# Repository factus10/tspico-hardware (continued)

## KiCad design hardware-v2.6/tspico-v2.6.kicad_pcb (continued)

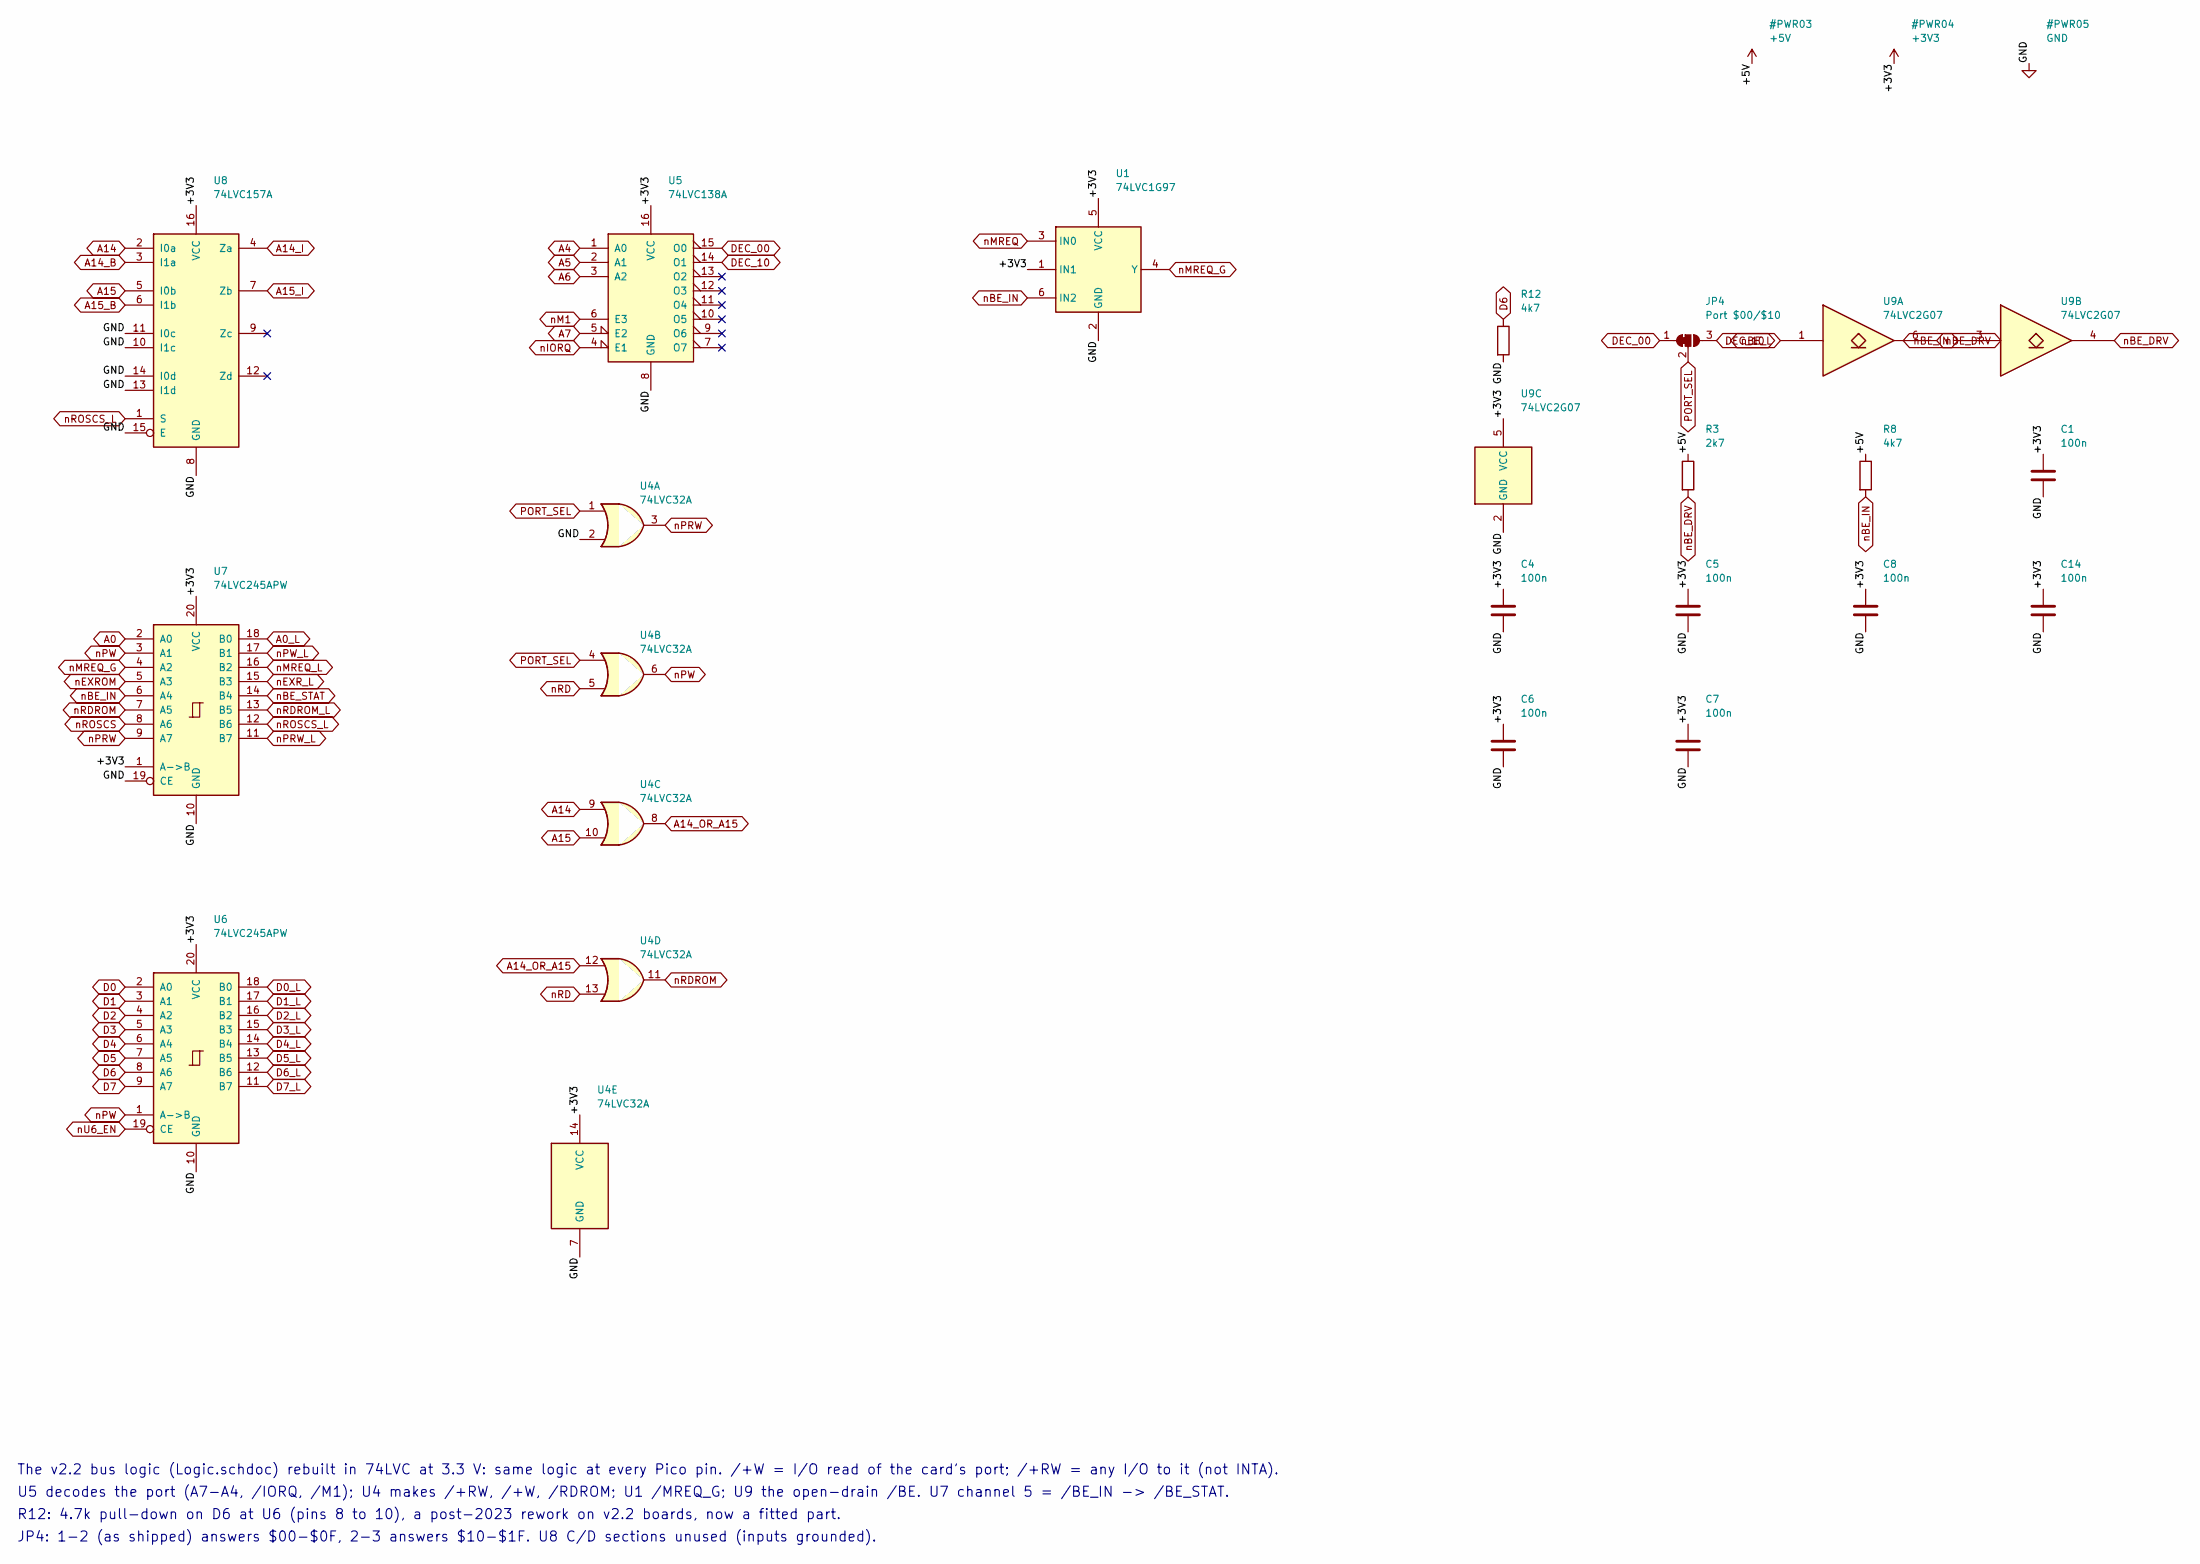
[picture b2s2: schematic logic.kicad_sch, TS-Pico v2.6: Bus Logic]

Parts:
C1, C4, C5, C6, C7, C8, C14: 100n; C_0603_1608Metric; MPN CC0603KRX7R9BB104; LCSC C14663
JP4: Port $00/$10; SolderJumper-3_P1.3mm_Bridged12_RoundedPad1.0x1.5mm_NumberL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
R3: 2k7; R_0603_1608Metric; MPN 0603WAF2701T5E; LCSC C13167
R8, R12: 4k7; R_0603_1608Metric; MPN 0603WAF4701T5E; LCSC C23162
U1: 74LVC1G97; SOT-23-6; MPN SN74LVC1G97DBVR; LCSC C128411
U4: 74LVC32A; TSSOP-14_4.4x5mm_P0.65mm; MPN 74LVC32APW,118; LCSC C6087
U5: 74LVC138A; TSSOP-16_4.4x5mm_P0.65mm; MPN SN74LVC138APWR; LCSC C485077
U6, U7: 74LVC245APW; TSSOP-20_4.4x6.5mm_P0.65mm; MPN 74LVC245APW,118; LCSC C6082
U8: 74LVC157A; TSSOP-16_4.4x5mm_P0.65mm; MPN SN74LVC157APWR; LCSC C406871
U9: 74LVC2G07; SOT-23-6; MPN 74LVC2G07GV; LCSC C19829597

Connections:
+3V3: C1.1, C4.1, C5.1, C6.1, C7.1, C8.1, C14.1, U1.1 (IN1), U1.5 (VCC), U4.14 (VCC), U5.16 (VCC), U6.20 (VCC), U7.1 (A->B), U7.20 (VCC), U8.16 (VCC), U9.5 (VCC); also elsewhere on the board
+5V: R3.1, R8.1; also elsewhere on the board
A0: U7.2 (A0); also elsewhere on the board
A0_L: U7.18 (B0); also elsewhere on the board
A4: U5.1 (A0); also elsewhere on the board
A5: U5.2 (A1); also elsewhere on the board
A6: U5.3 (A2); also elsewhere on the board
A7: U5.5 (E2); also elsewhere on the board
A14: U4.9, U8.2 (I0a); also elsewhere on the board
A14_B: U8.3 (I1a); also elsewhere on the board
A14_I: U8.4 (Za); also elsewhere on the board
A14_OR_A15: U4.8, U4.12
A15: U4.10, U8.5 (I0b); also elsewhere on the board
A15_B: U8.6 (I1b); also elsewhere on the board
A15_I: U8.7 (Zb); also elsewhere on the board
D0: U6.2 (A0); also elsewhere on the board
D0_L: U6.18 (B0); also elsewhere on the board
D1: U6.3 (A1); also elsewhere on the board
D1_L: U6.17 (B1); also elsewhere on the board
D2: U6.4 (A2); also elsewhere on the board
D2_L: U6.16 (B2); also elsewhere on the board
D3: U6.5 (A3); also elsewhere on the board
D3_L: U6.15 (B3); also elsewhere on the board
D4: U6.6 (A4); also elsewhere on the board
D4_L: U6.14 (B4); also elsewhere on the board
D5: U6.7 (A5); also elsewhere on the board
D5_L: U6.13 (B5); also elsewhere on the board
D6: R12.1, U6.8 (A6); also elsewhere on the board
D6_L: U6.12 (B6); also elsewhere on the board
D7: U6.9 (A7); also elsewhere on the board
D7_L: U6.11 (B7); also elsewhere on the board
DEC_00: JP4.1 (A), U5.15 (O0)
DEC_10: JP4.3 (B), U5.14 (O1)
GND: C1.2, C4.2, C5.2, C6.2, C7.2, C8.2, C14.2, R12.2, U1.2 (GND), U4.2, U4.7 (GND), U5.8 (GND), U6.10 (GND), U7.10 (GND), U7.19 (CE), U8.8 (GND), U8.10 (I1c), U8.11 (I0c), U8.13 (I1d), U8.14 (I0d), U8.15 (E), U9.2 (GND); also elsewhere on the board
PORT_SEL: JP4.2 (C), U4.1, U4.4
nBE_DRV: R3.2, U9.4, U9.6; also elsewhere on the board
nBE_IN: R8.2, U1.6 (IN2), U7.6 (A4), U9.3; also elsewhere on the board
nBE_L: U9.1; also elsewhere on the board
nBE_STAT: U7.14 (B4); also elsewhere on the board
nEXROM: U7.5 (A3); also elsewhere on the board
nEXR_L: U7.15 (B3); also elsewhere on the board
nIORQ: U5.4 (E1); also elsewhere on the board
nM1: U5.6 (E3); also elsewhere on the board
nMREQ: U1.3 (IN0); also elsewhere on the board
nMREQ_G: U1.4 (Y), U7.4 (A2)
nMREQ_L: U7.16 (B2); also elsewhere on the board
nPRW: U4.3, U7.9 (A7)
nPRW_L: U7.11 (B7); also elsewhere on the board
nPW: U4.6, U6.1 (A->B), U7.3 (A1)
nPW_L: U7.17 (B1); also elsewhere on the board
nRD: U4.5, U4.13; also elsewhere on the board
nRDROM: U4.11, U7.7 (A5)
nRDROM_L: U7.13 (B5); also elsewhere on the board
nROSCS: U7.8 (A6); also elsewhere on the board
nROSCS_L: U7.12 (B6), U8.1 (S); also elsewhere on the board
nU6_EN: U6.19 (CE); also elsewhere on the board

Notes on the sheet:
The v2.2 bus logic (Logic.schdoc) rebuilt in 74LVC at 3.3 V: same logic at every Pico pin. /+W = I/O read of the card's port; /+RW = any I/O to it (not INTA).
U5 decodes the port (A7-A4, /IORQ, /M1); U4 makes /+RW, /+W, /RDROM; U1 /MREQ_G; U9 the open-drain /BE. U7 channel 5 = /BE_IN -> /BE_STAT.
R12: 4.7k pull-down on D6 at U6 (pins 8 to 10), a post-2023 rework on v2.2 boards, now a fitted part.
JP4: 1-2 (as shipped) answers $00-$0F, 2-3 answers $10-$1F. U8 C/D sections unused (inputs grounded).

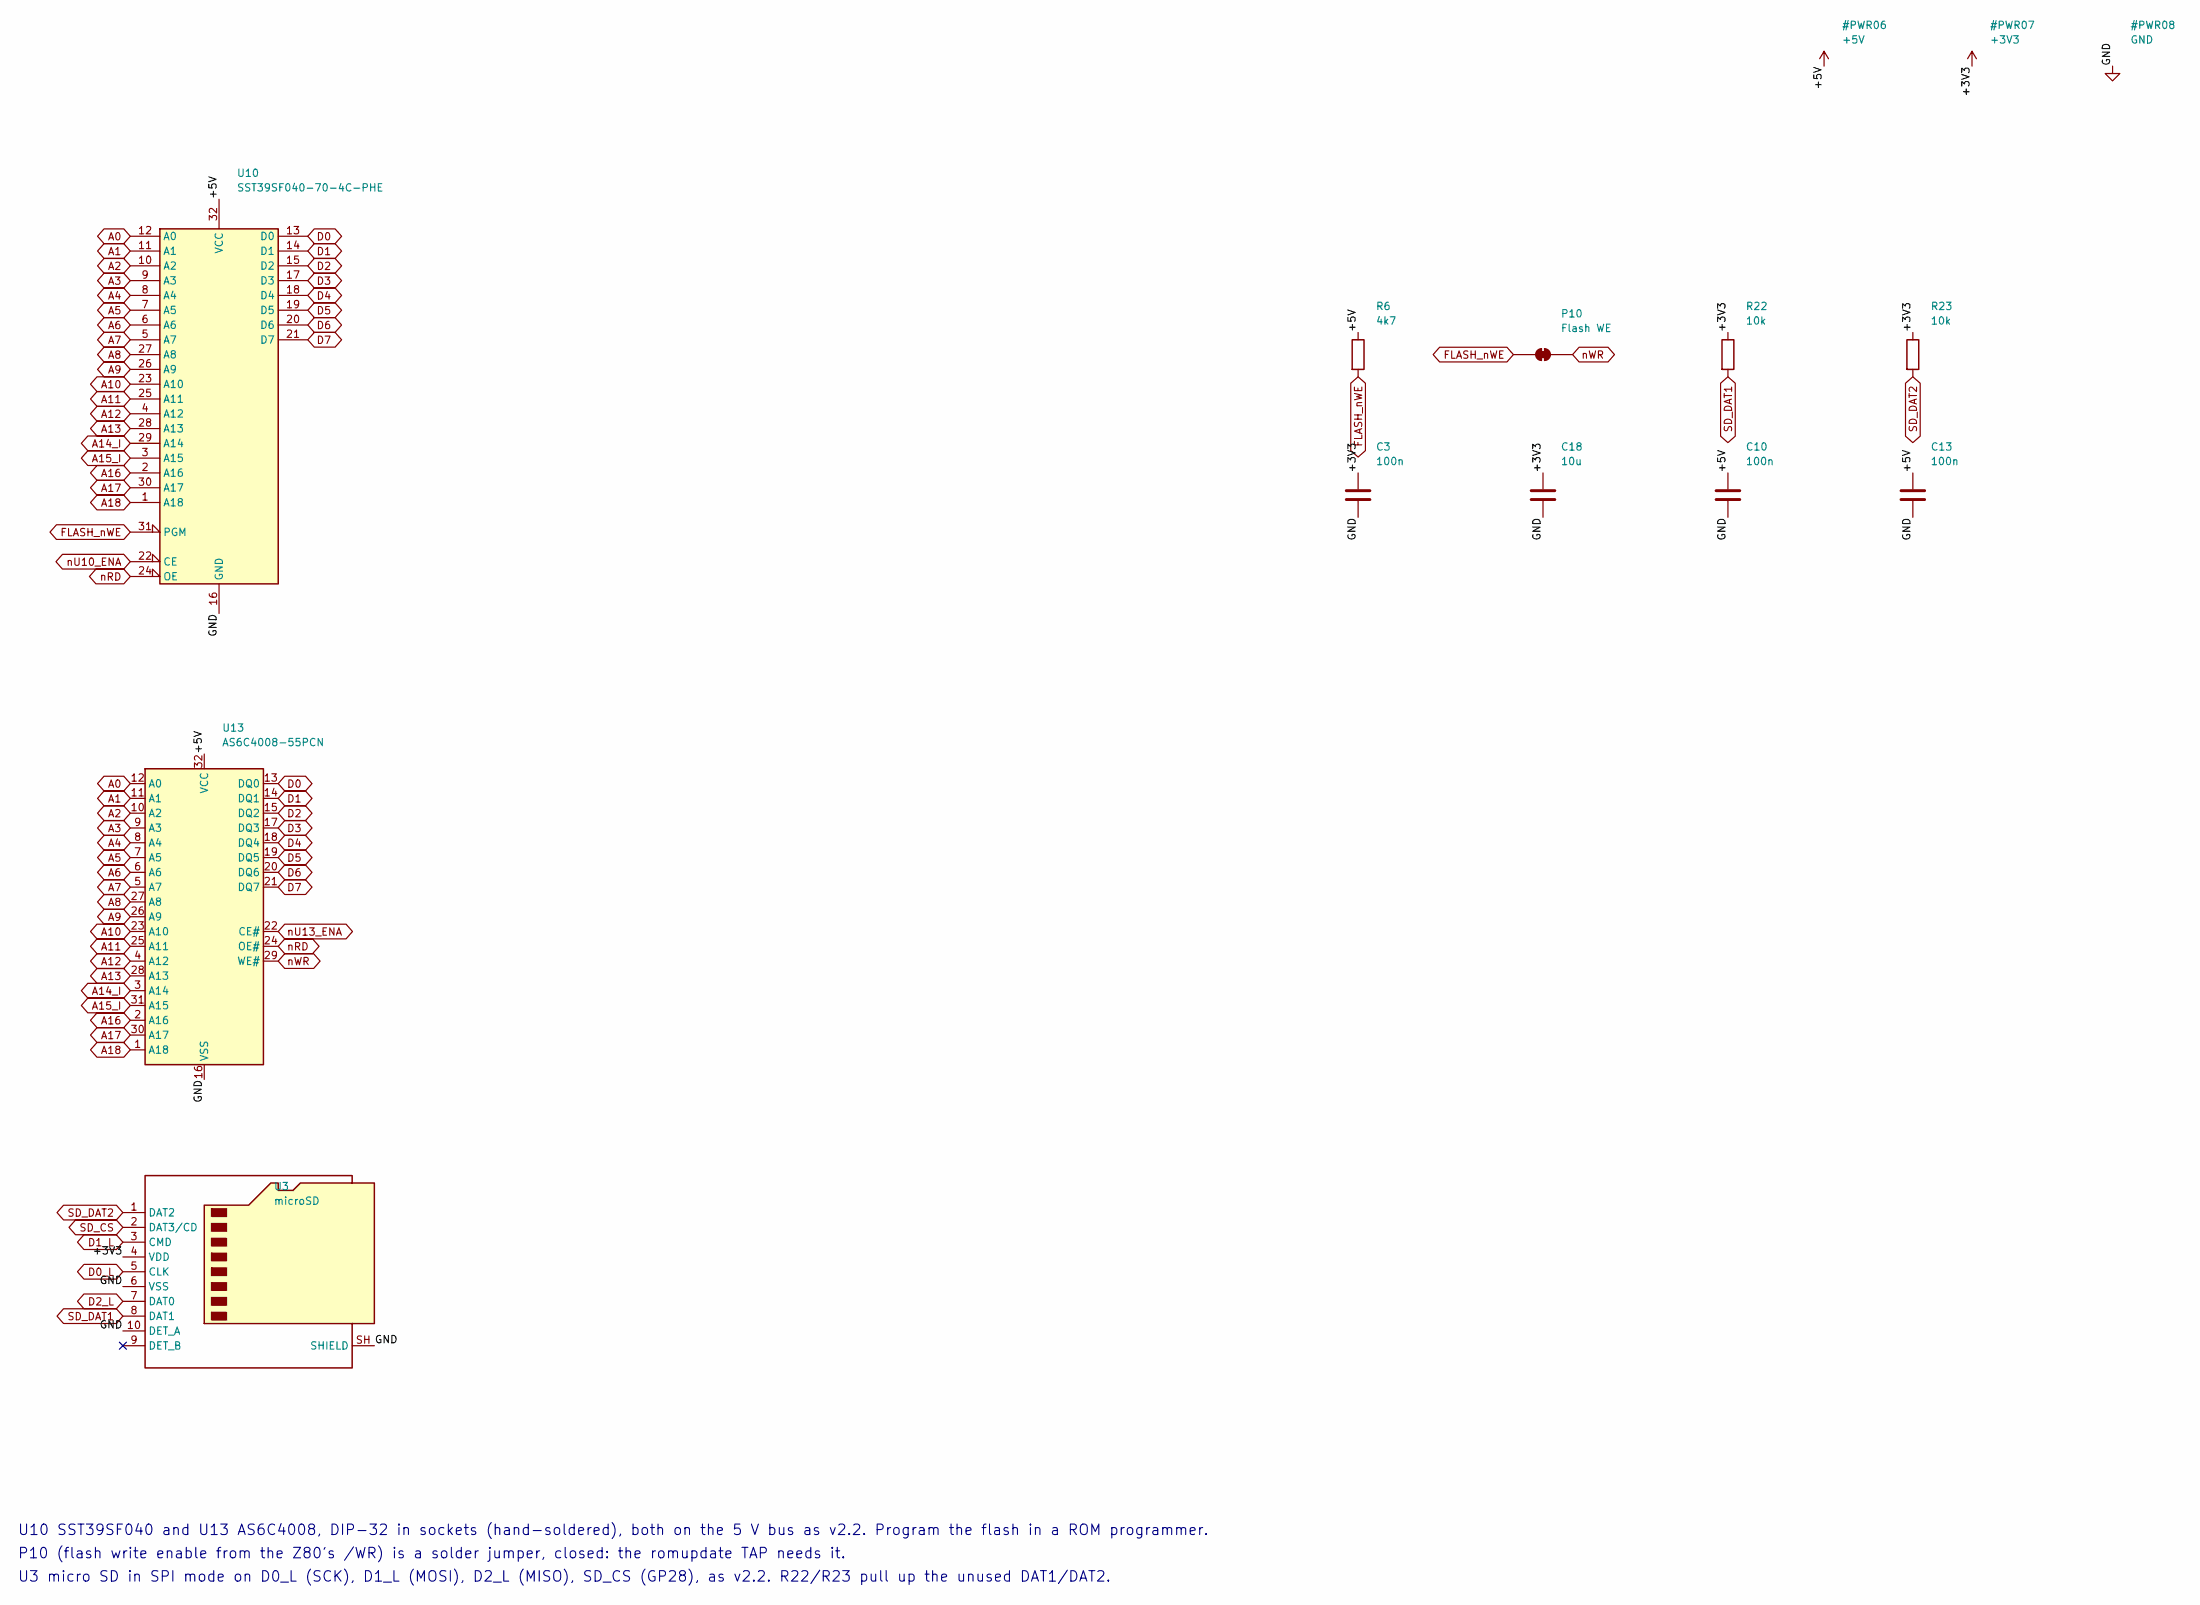
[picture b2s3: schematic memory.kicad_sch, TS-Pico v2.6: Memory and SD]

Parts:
C3, C10, C13: 100n; C_0603_1608Metric; MPN CC0603KRX7R9BB104; LCSC C14663
C18: 10u; C_0805_2012Metric; MPN CL21A106KAYNNNE; LCSC C15850
P10: Flash WE; SolderJumper-2_P1.3mm_Bridged_RoundedPad1.0x1.5mm
R6: 4k7; R_0603_1608Metric; MPN 0603WAF4701T5E; LCSC C23162
R22, R23: 10k; R_0603_1608Metric; MPN 0603WAF1002T5E; LCSC C25804
U3: microSD; microSD_TF-01A; MPN TF-01A; LCSC C91145
U10: SST39SF040-70-4C-PHE; DIP-32_W15.24mm_Socket
U13: AS6C4008-55PCN; DIP-32_W15.24mm_Socket

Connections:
+3V3: C3.1, C18.1, R22.1, R23.1, U3.4 (VDD); also elsewhere on the board
+5V: C10.1, C13.1, R6.1, U10.32 (VCC), U13.32 (VCC); also elsewhere on the board
A0: U10.12 (A0), U13.12 (A0); also elsewhere on the board
A1: U10.11 (A1), U13.11 (A1); also elsewhere on the board
A2: U10.10 (A2), U13.10 (A2); also elsewhere on the board
A3: U10.9 (A3), U13.9 (A3); also elsewhere on the board
A4: U10.8 (A4), U13.8 (A4); also elsewhere on the board
A5: U10.7 (A5), U13.7 (A5); also elsewhere on the board
A6: U10.6 (A6), U13.6 (A6); also elsewhere on the board
A7: U10.5 (A7), U13.5 (A7); also elsewhere on the board
A8: U10.27 (A8), U13.27 (A8); also elsewhere on the board
A9: U10.26 (A9), U13.26 (A9); also elsewhere on the board
A10: U10.23 (A10), U13.23 (A10); also elsewhere on the board
A11: U10.25 (A11), U13.25 (A11); also elsewhere on the board
A12: U10.4 (A12), U13.4 (A12); also elsewhere on the board
A13: U10.28 (A13), U13.28 (A13); also elsewhere on the board
A14_I: U10.29 (A14), U13.3 (A14); also elsewhere on the board
A15_I: U10.3 (A15), U13.31 (A15); also elsewhere on the board
A16: U10.2 (A16), U13.2 (A16); also elsewhere on the board
A17: U10.30 (A17), U13.30 (A17); also elsewhere on the board
A18: U10.1 (A18), U13.1 (A18); also elsewhere on the board
D0: U10.13 (D0), U13.13 (DQ0); also elsewhere on the board
D0_L: U3.5 (CLK); also elsewhere on the board
D1: U10.14 (D1), U13.14 (DQ1); also elsewhere on the board
D1_L: U3.3 (CMD); also elsewhere on the board
D2: U10.15 (D2), U13.15 (DQ2); also elsewhere on the board
D2_L: U3.7 (DAT0); also elsewhere on the board
D3: U10.17 (D3), U13.17 (DQ3); also elsewhere on the board
D4: U10.18 (D4), U13.18 (DQ4); also elsewhere on the board
D5: U10.19 (D5), U13.19 (DQ5); also elsewhere on the board
D6: U10.20 (D6), U13.20 (DQ6); also elsewhere on the board
D7: U10.21 (D7), U13.21 (DQ7); also elsewhere on the board
FLASH_nWE: P10.1 (A), R6.2, U10.31 (PGM)
GND: C3.2, C10.2, C13.2, C18.2, U3.6 (VSS), U3.10 (DET_A), U3.SH (SHIELD), U10.16 (GND), U13.16 (VSS); also elsewhere on the board
SD_CS: U3.2 (DAT3/CD); also elsewhere on the board
SD_DAT1: R22.2, U3.8 (DAT1)
SD_DAT2: R23.2, U3.1 (DAT2)
nRD: U10.24 (OE), U13.24 (OE#); also elsewhere on the board
nU10_ENA: U10.22 (CE); also elsewhere on the board
nU13_ENA: U13.22 (CE#); also elsewhere on the board
nWR: P10.2 (B), U13.29 (WE#); also elsewhere on the board

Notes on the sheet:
U10 SST39SF040 and U13 AS6C4008, DIP-32 in sockets (hand-soldered), both on the 5 V bus as v2.2. Program the flash in a ROM programmer.
P10 (flash write enable from the Z80's /WR) is a solder jumper, closed: the romupdate TAP needs it.
U3 micro SD in SPI mode on D0_L (SCK), D1_L (MOSI), D2_L (MISO), SD_CS (GP28), as v2.2. R22/R23 pull up the unused DAT1/DAT2.

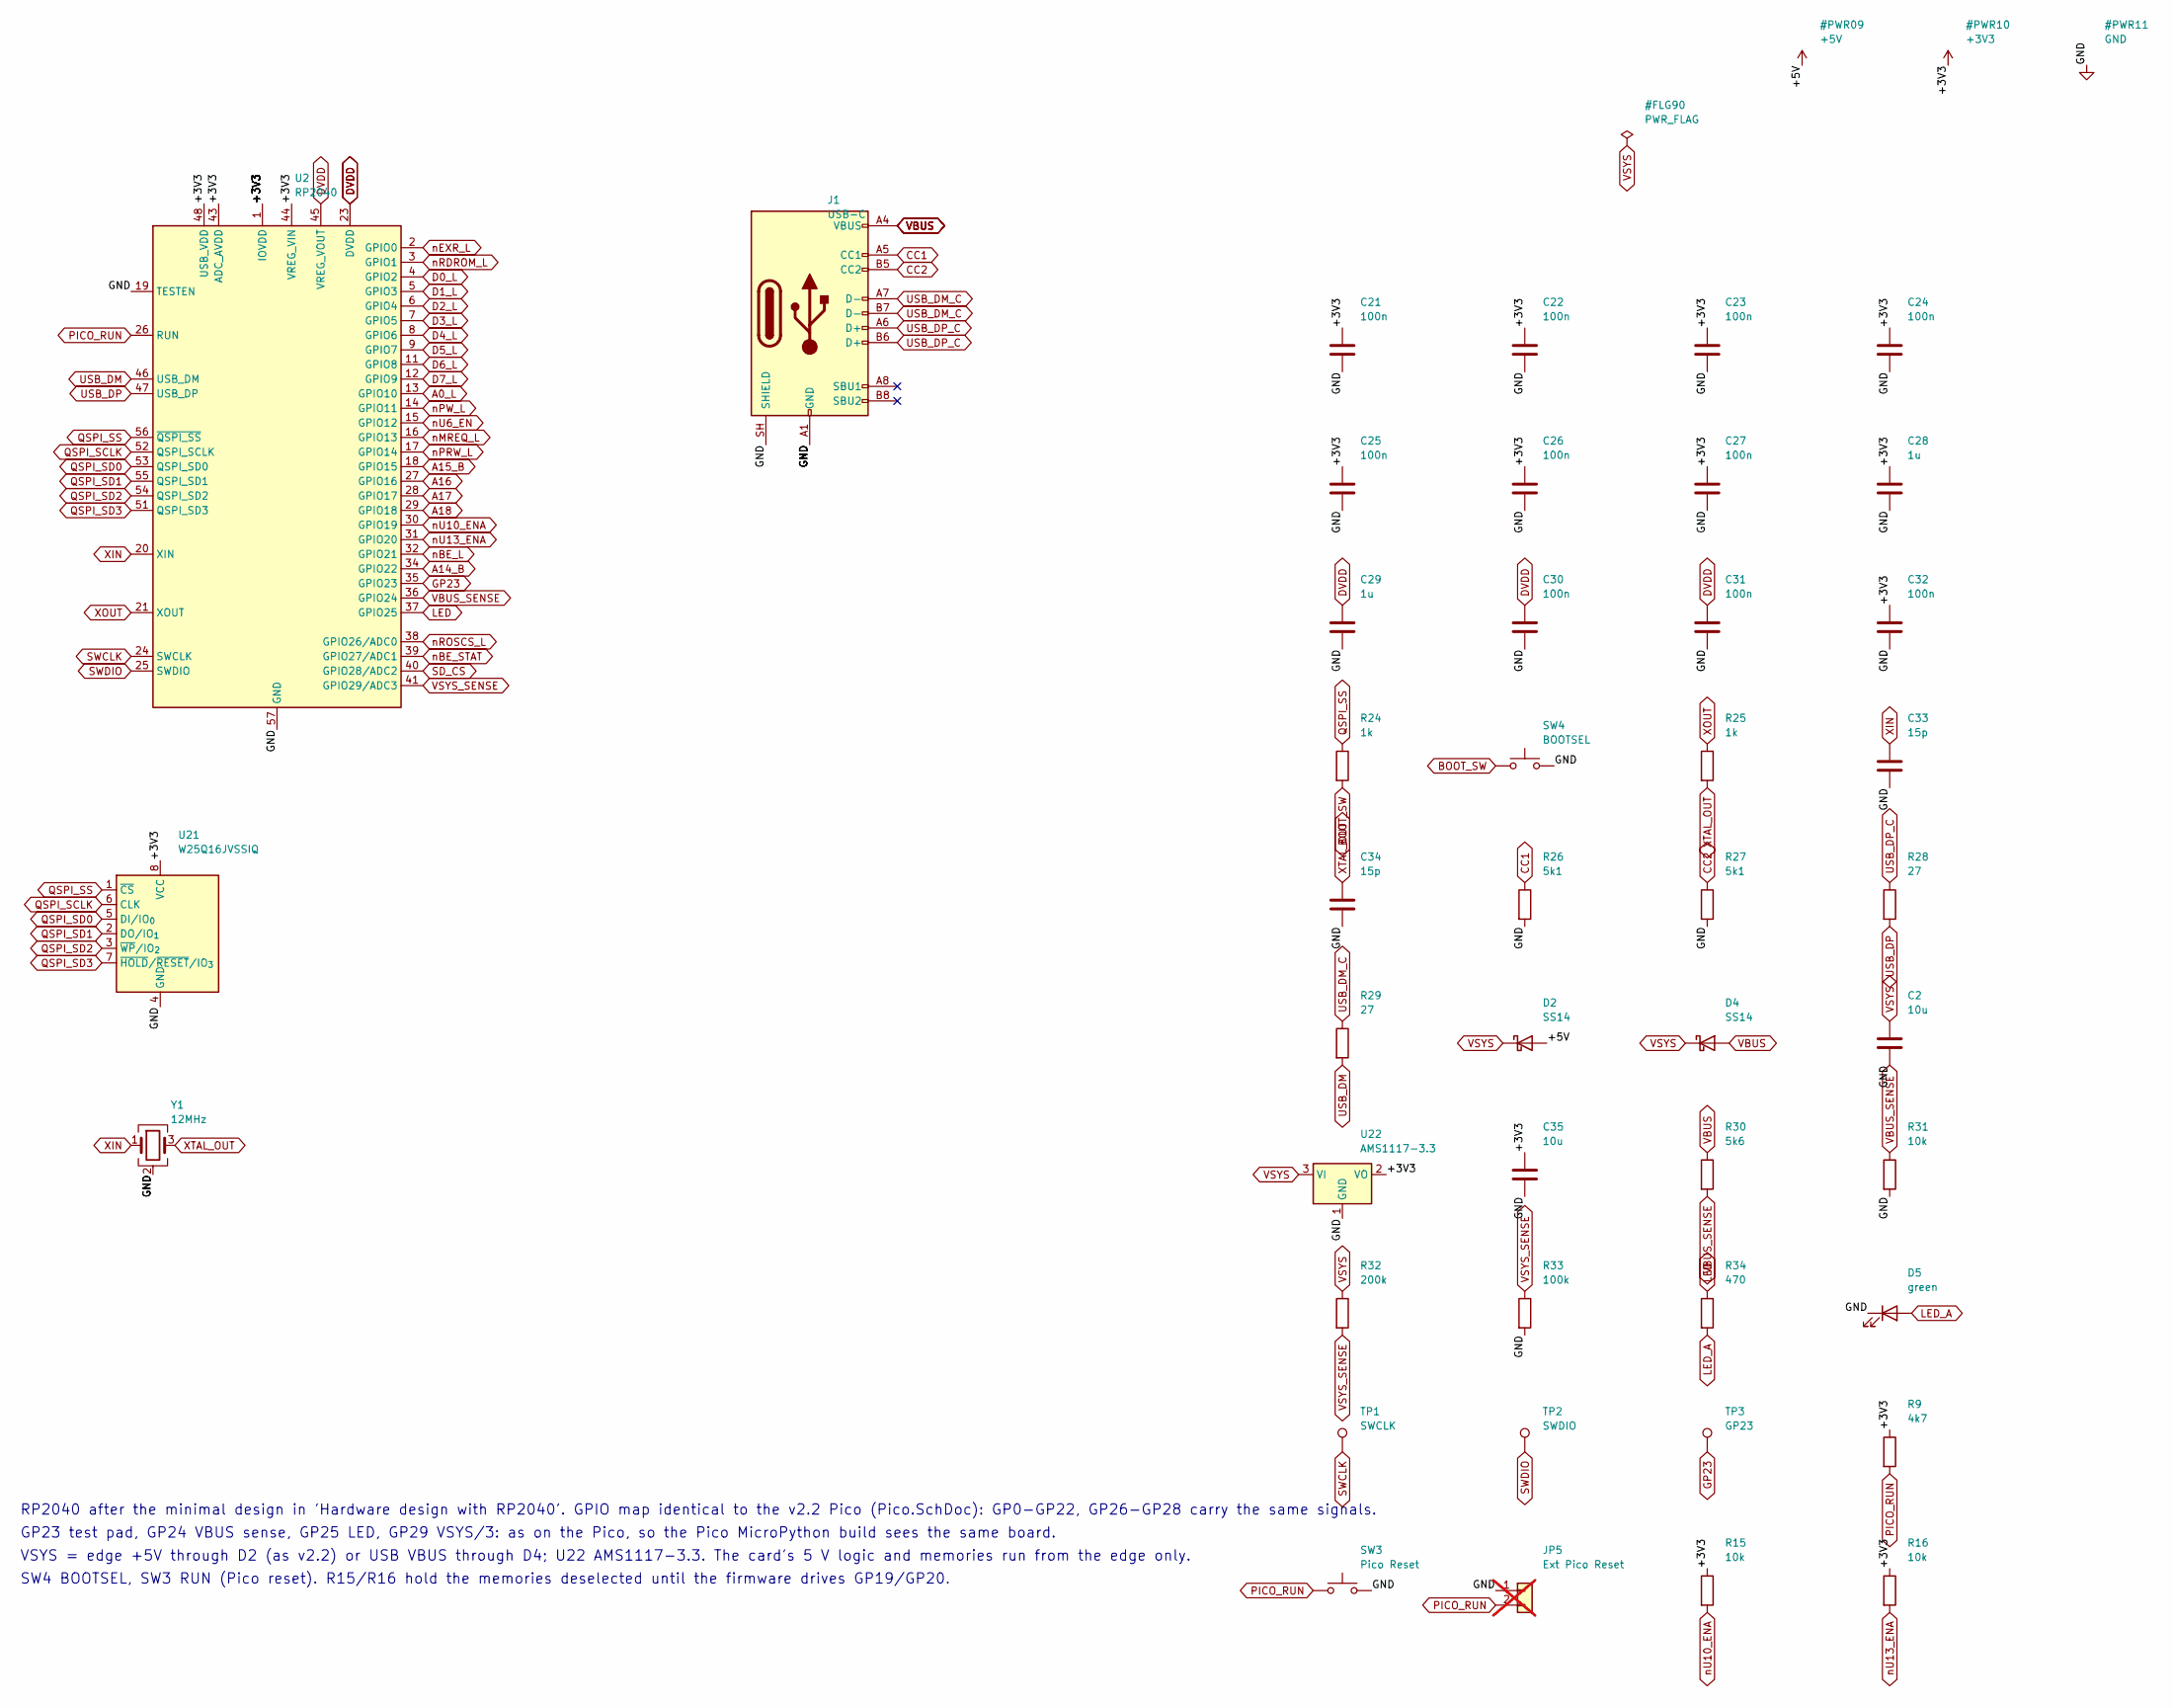
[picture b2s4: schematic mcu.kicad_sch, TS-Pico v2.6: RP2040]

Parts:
C2, C35: 10u; C_0805_2012Metric; MPN CL21A106KAYNNNE; LCSC C15850
C21, C22, C23, C24, C25, C26, C27, C30, C31, C32: 100n; C_0603_1608Metric; MPN CC0603KRX7R9BB104; LCSC C14663
C28, C29: 1u; C_0603_1608Metric; MPN CL10A105KB8NNNC; LCSC C15849
C33, C34: 15p; C_0603_1608Metric; MPN CL10C150JB8NNNC; LCSC C1644
D2, D4: SS14; D_SMA; MPN SS14; LCSC C2480
D5: green; LED_0805_2012Metric; MPN KT-0805G; LCSC C2297
J1: USB-C; USB_C_Receptacle_HRO_TYPE-C-31-M-12; MPN TYPE-C-31-M-12; LCSC C165948
JP5: Ext Pico Reset; PinHeader_1x02_P2.54mm_Vertical_SMD_Pin1Left; not fitted
R9: 4k7; R_0603_1608Metric; MPN 0603WAF4701T5E; LCSC C23162
R15, R16, R31: 10k; R_0603_1608Metric; MPN 0603WAF1002T5E; LCSC C25804
R24, R25: 1k; R_0603_1608Metric; MPN 0603WAF1001T5E; LCSC C21190
R26, R27: 5k1; R_0603_1608Metric; MPN 0603WAF5101T5E; LCSC C23186
R28, R29: 27; R_0603_1608Metric; MPN 0603WAF270JT5E; LCSC C25190
R30: 5k6; R_0603_1608Metric; MPN 0603WAF5601T5E; LCSC C23189
R32: 200k; R_0603_1608Metric; MPN 0603WAF2003T5E; LCSC C25811
R33: 100k; R_0603_1608Metric; MPN 0603WAF1003T5E; LCSC C25803
R34: 470; R_0603_1608Metric; MPN 0603WAF4700T5E; LCSC C23179
SW3: Pico Reset; SW_Push_1P1T_XKB_TS-1187A; MPN TS-1187A-B-A-B; LCSC C318884
SW4: BOOTSEL; SW_Push_1P1T_XKB_TS-1187A; MPN TS-1187A-B-A-B; LCSC C318884
TP1: SWCLK; TestPoint_Pad_D1.0mm
TP2: SWDIO; TestPoint_Pad_D1.0mm
TP3: GP23; TestPoint_Pad_D1.0mm
U2: RP2040; QFN-56-1EP_7x7mm_P0.4mm_EP3.2x3.2mm; MPN RP2040; LCSC C2040
U21: W25Q16JVSSIQ; SOIC-8_5.3x5.3mm_P1.27mm; MPN W25Q16JVSSIQ; LCSC C82317
U22: AMS1117-3.3; SOT-223-3_TabPin2; MPN AMS1117-3.3; LCSC C6186
Y1: 12MHz; Crystal_SMD_3225-4Pin_3.2x2.5mm; MPN ABM8-272-T3; LCSC C20625731

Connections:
+3V3: C21.1, C22.1, C23.1, C24.1, C25.1, C26.1, C27.1, C28.1, C32.1, C35.1, R9.1, R15.1, R16.1, U2.1 (IOVDD), U2.10 (IOVDD), U2.22 (IOVDD), U2.33 (IOVDD), U2.42 (IOVDD), U2.43 (ADC_AVDD), U2.44 (VREG_VIN), U2.48 (USB_VDD), U2.49 (IOVDD), U21.8 (VCC), U22.2 (VO); also elsewhere on the board
+5V: D2.2 (A); also elsewhere on the board
A0_L: U2.13 (GPIO10); also elsewhere on the board
A14_B: U2.34 (GPIO22); also elsewhere on the board
A15_B: U2.18 (GPIO15); also elsewhere on the board
A16: U2.27 (GPIO16); also elsewhere on the board
A17: U2.28 (GPIO17); also elsewhere on the board
A18: U2.29 (GPIO18); also elsewhere on the board
BOOT_SW: R24.2, SW4.1
CC1: J1.A5 (CC1), R26.1
CC2: J1.B5 (CC2), R27.1
D0_L: U2.4 (GPIO2); also elsewhere on the board
D1_L: U2.5 (GPIO3); also elsewhere on the board
D2_L: U2.6 (GPIO4); also elsewhere on the board
D3_L: U2.7 (GPIO5); also elsewhere on the board
D4_L: U2.8 (GPIO6); also elsewhere on the board
D5_L: U2.9 (GPIO7); also elsewhere on the board
D6_L: U2.11 (GPIO8); also elsewhere on the board
D7_L: U2.12 (GPIO9); also elsewhere on the board
DVDD: C29.1, C30.1, C31.1, U2.23 (DVDD), U2.45 (VREG_VOUT), U2.50 (DVDD)
GND: C2.2, C21.2, C22.2, C23.2, C24.2, C25.2, C26.2, C27.2, C28.2, C29.2, C30.2, C31.2, C32.2, C33.2, C34.2, C35.2, D5.1 (K), J1.A1 (GND), J1.A12 (GND), J1.B1 (GND), J1.B12 (GND), J1.SH (SHIELD), JP5.1, R26.2, R27.2, R31.2, R33.2, SW3.2, SW4.2, U2.19 (TESTEN), U2.57 (GND), U21.4 (GND), U22.1 (GND), Y1.2 (G), Y1.4 (G); also elsewhere on the board
GP23: TP3.1, U2.35 (GPIO23)
LED: R34.1, U2.37 (GPIO25)
LED_A: D5.2 (A), R34.2
PICO_RUN: JP5.2, R9.2, SW3.1, U2.26 (RUN)
QSPI_SCLK: U2.52 (QSPI_SCLK), U21.6 (CLK)
QSPI_SD0: U2.53 (QSPI_SD0), U21.5 (DI/IO_{0})
QSPI_SD1: U2.55 (QSPI_SD1), U21.2 (DO/IO_{1})
QSPI_SD2: U2.54 (QSPI_SD2), U21.3 (~WP/IO_{2})
QSPI_SD3: U2.51 (QSPI_SD3), U21.7 (~HOLD/~RESET/IO_{3})
QSPI_SS: R24.1, U2.56 (~QSPI_SS), U21.1 (~CS)
SD_CS: U2.40 (GPIO28/ADC2); also elsewhere on the board
SWCLK: TP1.1, U2.24 (SWCLK)
SWDIO: TP2.1, U2.25 (SWDIO)
USB_DM: R29.2, U2.46 (USB_DM)
USB_DM_C: J1.A7 (D-), J1.B7 (D-), R29.1
USB_DP: R28.2, U2.47 (USB_DP)
USB_DP_C: J1.A6 (D+), J1.B6 (D+), R28.1
VBUS: D4.2 (A), J1.A4 (VBUS), J1.A9 (VBUS), J1.B4 (VBUS), J1.B9 (VBUS), R30.1
VBUS_SENSE: R30.2, R31.1, U2.36 (GPIO24)
VSYS: C2.1, D2.1 (K), D4.1 (K), R32.1, U22.3 (VI)
VSYS_SENSE: R32.2, R33.1, U2.41 (GPIO29/ADC3)
XIN: C33.1, U2.20 (XIN), Y1.1
XOUT: R25.1, U2.21 (XOUT)
XTAL_OUT: C34.1, R25.2, Y1.3
nBE_L: U2.32 (GPIO21); also elsewhere on the board
nBE_STAT: U2.39 (GPIO27/ADC1); also elsewhere on the board
nEXR_L: U2.2 (GPIO0); also elsewhere on the board
nMREQ_L: U2.16 (GPIO13); also elsewhere on the board
nPRW_L: U2.17 (GPIO14); also elsewhere on the board
nPW_L: U2.14 (GPIO11); also elsewhere on the board
nRDROM_L: U2.3 (GPIO1); also elsewhere on the board
nROSCS_L: U2.38 (GPIO26/ADC0); also elsewhere on the board
nU6_EN: U2.15 (GPIO12); also elsewhere on the board
nU10_ENA: R15.2, U2.30 (GPIO19); also elsewhere on the board
nU13_ENA: R16.2, U2.31 (GPIO20); also elsewhere on the board

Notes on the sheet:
RP2040 after the minimal design in 'Hardware design with RP2040'. GPIO map identical to the v2.2 Pico (Pico.SchDoc): GP0-GP22, GP26-GP28 carry the same signals.
GP23 test pad, GP24 VBUS sense, GP25 LED, GP29 VSYS/3: as on the Pico, so the Pico MicroPython build sees the same board.
VSYS = edge +5V through D2 (as v2.2) or USB VBUS through D4; U22 AMS1117-3.3. The card's 5 V logic and memories run from the edge only.
SW4 BOOTSEL, SW3 RUN (Pico reset). R15/R16 hold the memories deselected until the firmware drives GP19/GP20.

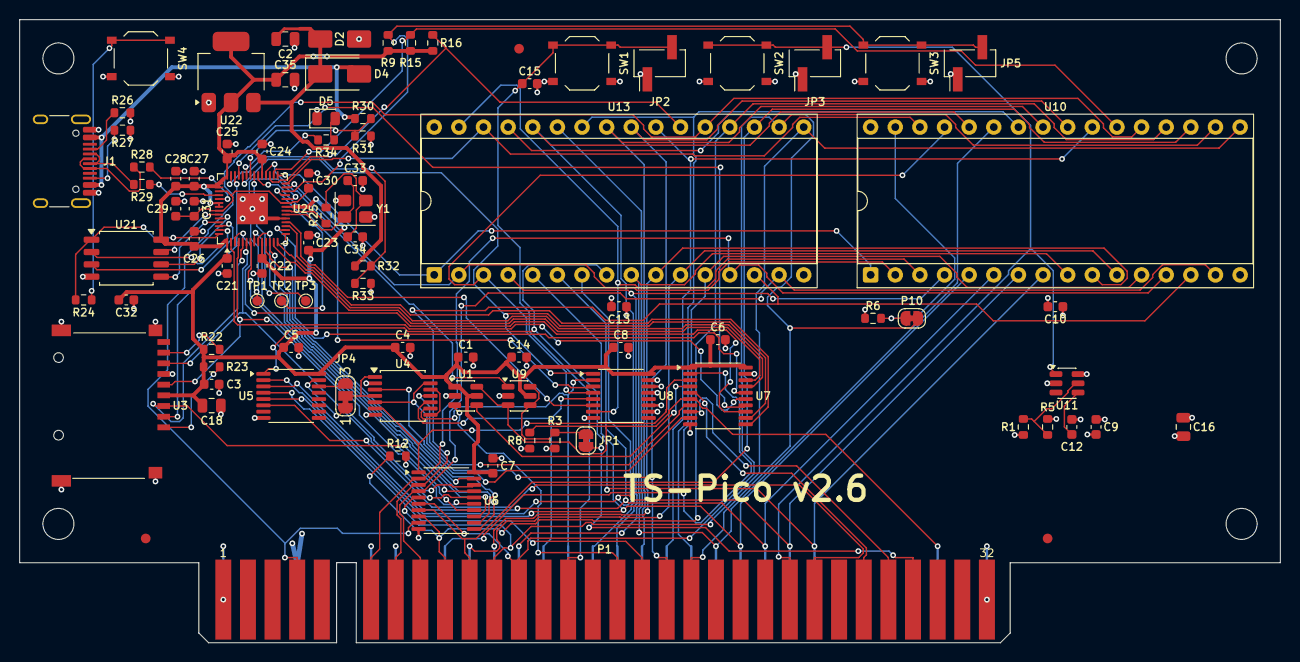
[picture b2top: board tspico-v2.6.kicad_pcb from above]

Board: 4 copper layers, 130.0 x 64.2 mm, 93 parts (0 on the bottom side), 107 nets.

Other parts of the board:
FID1, FID2, FID3: Fiducial_1mm_Mask2mm
H1, H2, H3, H4: MountingHole_3.2mm_M3

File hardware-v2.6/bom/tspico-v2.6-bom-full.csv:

"Value","Reference","Footprint","MPN","LCSC","Qty"
"100n","C1,C3-C10,C13-C15,C21-C27,C30-C32","Capacitor_SMD:C_0603_1608Metric","CC0603KRX7R9BB104","C14663","22"
"10u","C2,C16,C18,C35","Capacitor_SMD:C_0805_2012Metric","CL21A106KAYNNNE","C15850","4"
"470n","C12","Capacitor_SMD:C_0603_1608Metric","CL10B474KA8NNNC","C1623","1"
"1u","C28,C29","Capacitor_SMD:C_0603_1608Metric","CL10A105KB8NNNC","C15849","2"
"15p","C33,C34","Capacitor_SMD:C_0603_1608Metric","CL10C150JB8NNNC","C1644","2"
"SS14","D2,D4","Diode_SMD:D_SMA","SS14","C2480","2"
"green","D5","LED_SMD:LED_0805_2012Metric","KT-0805G","C2297","1"
"USB-C","J1","Connector_USB:USB_C_Receptacle_HRO_TYPE-C-31-M-12","TYPE-C-31-M-12","C165948","1"
"BE link","JP1","Jumper:SolderJumper-2_P1.3mm_Bridged_RoundedPad1.0x1.5mm","","","1"
"Port $00/$10","JP4","Jumper:SolderJumper-3_P1.3mm_Bridged12_RoundedPad1.0x1.5mm_NumberLabels","","","1"
"TS2068_Edge","P1","tspico:TS2068_EdgeConnector_2x32","","","1"
"Flash WE","P10","Jumper:SolderJumper-2_P1.3mm_Bridged_RoundedPad1.0x1.5mm","","","1"
"100k","R1,R33","Resistor_SMD:R_0603_1608Metric","0603WAF1003T5E","C25803","2"
"2k7","R3","Resistor_SMD:R_0603_1608Metric","0603WAF2701T5E","C13167","1"
"11k","R5","Resistor_SMD:R_0603_1608Metric","0603WAF1102T5E","C25950","1"
"4k7","R6,R8,R9,R12","Resistor_SMD:R_0603_1608Metric","0603WAF4701T5E","C23162","4"
"10k","R15,R16,R22,R23,R31","Resistor_SMD:R_0603_1608Metric","0603WAF1002T5E","C25804","5"
"1k","R24,R25","Resistor_SMD:R_0603_1608Metric","0603WAF1001T5E","C21190","2"
"5k1","R26,R27","Resistor_SMD:R_0603_1608Metric","0603WAF5101T5E","C23186","2"
"27","R28,R29","Resistor_SMD:R_0603_1608Metric","0603WAF270JT5E","C25190","2"
"5k6","R30","Resistor_SMD:R_0603_1608Metric","0603WAF5601T5E","C23189","1"
"200k","R32","Resistor_SMD:R_0603_1608Metric","0603WAF2003T5E","C25811","1"
"470","R34","Resistor_SMD:R_0603_1608Metric","0603WAF4700T5E","C23179","1"
"NMI","SW1","Button_Switch_SMD:SW_Push_1P1T_XKB_TS-1187A","TS-1187A-B-A-B","C318884","1"
"TS Reset","SW2","Button_Switch_SMD:SW_Push_1P1T_XKB_TS-1187A","TS-1187A-B-A-B","C318884","1"
"Pico Reset","SW3","Button_Switch_SMD:SW_Push_1P1T_XKB_TS-1187A","TS-1187A-B-A-B","C318884","1"
"BOOTSEL","SW4","Button_Switch_SMD:SW_Push_1P1T_XKB_TS-1187A","TS-1187A-B-A-B","C318884","1"
"SWCLK","TP1","TestPoint:TestPoint_Pad_D1.0mm","","","1"
"SWDIO","TP2","TestPoint:TestPoint_Pad_D1.0mm","","","1"
"GP23","TP3","TestPoint:TestPoint_Pad_D1.0mm","","","1"
"74LVC1G97","U1","Package_TO_SOT_SMD:SOT-23-6","SN74LVC1G97DBVR","C128411","1"
"RP2040","U2","Package_DFN_QFN:QFN-56-1EP_7x7mm_P0.4mm_EP3.2x3.2mm","RP2040","C2040","1"
"microSD","U3","tspico:microSD_TF-01A","TF-01A","C91145","1"
"74LVC32A","U4","Package_SO:TSSOP-14_4.4x5mm_P0.65mm","74LVC32APW,118","C6087","1"
"74LVC138A","U5","Package_SO:TSSOP-16_4.4x5mm_P0.65mm","SN74LVC138APWR","C485077","1"
"74LVC245APW","U6,U7","Package_SO:TSSOP-20_4.4x6.5mm_P0.65mm","74LVC245APW,118","C6082","2"
"74LVC157A","U8","Package_SO:TSSOP-16_4.4x5mm_P0.65mm","SN74LVC157APWR","C406871","1"
"74LVC2G07","U9","Package_TO_SOT_SMD:SOT-23-6","74LVC2G07GV","C19829597","1"
"SST39SF040-70-4C-PHE","U10","Package_DIP:DIP-32_W15.24mm_Socket","","","1"
"TPS3808G01","U11","Package_TO_SOT_SMD:SOT-23-6","TPS3808G01DBVR","C19653","1"
"AS6C4008-55PCN","U13","Package_DIP:DIP-32_W15.24mm_Socket","","","1"
"W25Q16JVSSIQ","U21","Package_SO:SOIC-8_5.3x5.3mm_P1.27mm","W25Q16JVSSIQ","C82317","1"
"AMS1117-3.3","U22","Package_TO_SOT_SMD:SOT-223-3_TabPin2","AMS1117-3.3","C6186","1"
"12MHz","Y1","Crystal:Crystal_SMD_3225-4Pin_3.2x2.5mm","ABM8-272-T3","C20625731","1"
